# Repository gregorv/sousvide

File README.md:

# sousvide
An ATmega8 based Sous-Vide Temperature Controller

Sous-Vide is a cooking method for a very gentle preparation of meat and vegetables. The general idea is sealing the
food in a vacuum bed and then cooking it in a water bath with a maximum temperature of about 60°C to 70°C for an extended time.
Important cooking reactions (including sterilization) start at around 50°C, but unwanted processes (e.g. meat getting stringy)
increase above 70°C. Because of the lower temperatures the cooking time is elonged, but you get a very even and reproducible
result from the process.

## Overview
### Hardware
On the hardware side (schematics and layout KiCAD format) an ATmega8 regulates the temperature of the water bath with a TRIAC
controlled immersion heater. It is advised to use an acquarium water pump to better spread the heat in the bath. A DS18x2x type
Dallas 1Wire sensor is used for temperature monitoring. The UART can be used to communicate with a ESP8266 type WiFi module, but
is used in the prototype for serial communication and control.

### Firmware
A straight-forward, modularized fixed-point PID controller.

Uses the UART library from Peter Fleury, the 1wire library by Peter Dannegger and the libfixmath by Ben Brewer.

### PC Control Software
Qt5, QCustomPlot, nice.

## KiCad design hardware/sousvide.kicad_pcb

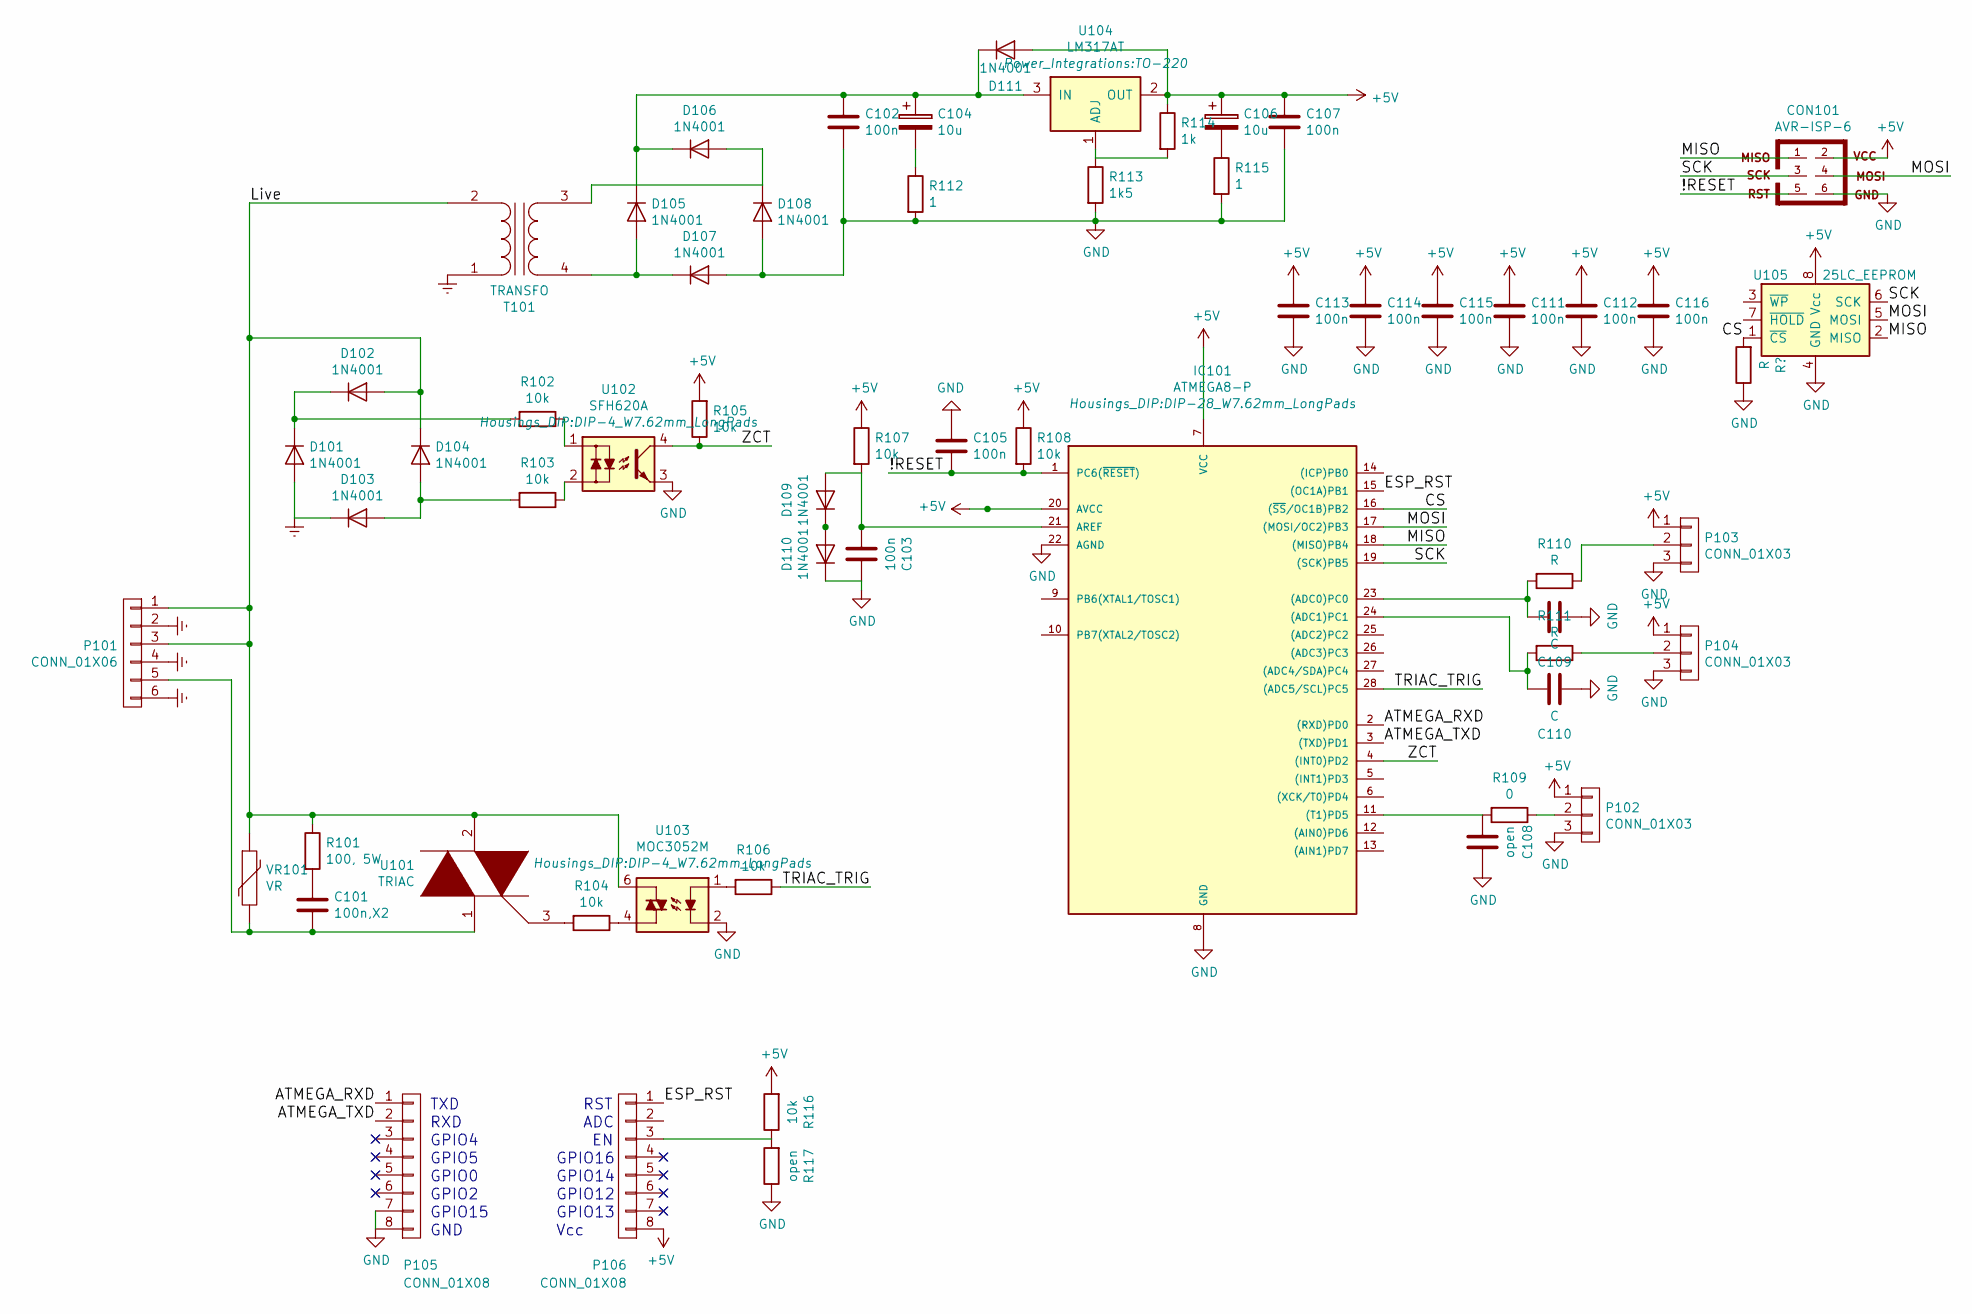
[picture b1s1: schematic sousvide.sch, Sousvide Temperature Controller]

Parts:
C101: 100n,X2; C_Rect_L18_W6_P15
C102, C103, C105, C107, C111, C112, C113, C114, C115, C116: 100n; C_0603_HandSoldering
C104, C106: 10u; TantalC_SizeB_EIA-3528_HandSoldering
C108: open; C_0603_HandSoldering
C109, C110: C; C_0603_HandSoldering
CON101: AVR-ISP-6; Pin_Header_Straight_2x03
D101, D102, D103, D104, D105, D106, D107, D108, D109, D110, D111: 1N4001; Diode_DO-41_SOD81_Horizontal_RM10
IC101: ATMEGA8-P; DIP-28_W7.62mm_LongPads
P101: CONN_01X06; TerminalBlock_Pheonix_MKDS1.5-6pol
P102, P103, P104: CONN_01X03; TerminalBlock_Pheonix_MKDS1.5-3pol
P105, P106: CONN_01X08; Connectors_JST_B8B-PH-K
R101: 100, 5W; Resistor_Horizontal_RM15mm
R102, R103, R104: 10k; Resistor_Horizontal_RM10mm
R105, R106, R107, R108, R116: 10k; R_0603_HandSoldering
R109: 0; R_0603_HandSoldering
R110, R111: R; R_0603_HandSoldering
R112, R115: 1; R_0603_HandSoldering
R113: 1k5; R_0603_HandSoldering
R114: 1k; R_0603_HandSoldering
R117: open; R_0603_HandSoldering
T101: TRANSFO; BLOCK_VB2,0_1_XX
U101: TRIAC; TO-220_Neutral123_Vertical_LargePads
U102: SFH620A; DIP-4_W7.62mm_LongPads
U103: MOC3052M; DIP-4_W7.62mm_LongPads
U104: LM317AT; TO-220
U105: 25LC_EEPROM; SOIC-8_3.9x4.9mm_Pitch1.27mm
VR101: VR; RV_Disc_D12_W4.2_P7.5

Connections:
+5V: C106.1, C107.1, C111.2, C112.2, C113.2, C114.2, C115.2, C116.2, CON101.2, D111.2 (A), IC101.7 (VCC), IC101.20 (AVCC), P102.1, P103.1, P104.1, P106.8, R105.2, R107.1, R108.1, R114.1, R116.2, U104.2 (OUT), U105.8 (Vcc)
/!RESET: C105.1, CON101.5, IC101.1 (PC6(~RESET~)), R108.2
/ATMEGA_RXD: IC101.2 ((RXD)PD0), P105.1
/ATMEGA_TXD: IC101.3 ((TXD)PD1), P105.2
/CS: IC101.16 ((~SS~/OC1B)PB2), U105.1 (~CS)
/ESP_RST: IC101.15 ((OC1A)PB1), P106.1
/Live: D102.2 (A), D104.1 (K), P101.1, P101.3, R101.1, T101.2 (AB), U101.2, U103.6, VR101.1
/MISO: CON101.1, IC101.18 ((MISO)PB4), U105.2 (MISO)
/MOSI: CON101.4, IC101.17 ((MOSI/OC2)PB3), U105.5 (MOSI)
/SCK: CON101.3, IC101.19 ((SCK)PB5), U105.6 (SCK)
/TRIAC_TRIG: IC101.28 ((ADC5/SCL)PC5), R106.1
/ZCT: IC101.4 ((INT0)PD2), R105.1, U102.4
Earth: D101.2 (A), D103.1 (K), P101.2, P101.4, P101.6, T101.1 (AA)
GND: C102.2, C103.1, C105.2, C107.2, C108.1, C109.2, C110.2, C111.1, C112.1, C113.1, C114.1, C115.1, C116.1, CON101.6, D107.2 (A), D108.2 (A), D110.1 (K), IC101.8 (GND), IC101.22 (AGND), P102.3, P103.3, P104.3, P105.7, P105.8, R112.2, R113.2, R115.2, R117.1, U102.3, U103.2, U105.4 (GND)
unnamed: C101.1, R101.2
unnamed: C101.2, P101.5, U101.1, VR101.2
unnamed: C102.1, C104.1, D105.1 (K), D106.1 (K), D111.1 (K), U104.3 (IN)
unnamed: C103.2, D109.2 (A), IC101.21 (AREF), R107.2
unnamed: C104.2, R112.1
unnamed: C106.2, R115.1
unnamed: C108.2, IC101.11 ((T1)PD5), R109.2
unnamed: C109.1, IC101.23 ((ADC0)PC0), R110.2
unnamed: C110.1, IC101.24 ((ADC1)PC1), R111.2
unnamed: D101.1 (K), D102.1 (K), R102.2
unnamed: D103.2 (A), D104.2 (A), R103.2
unnamed: D105.2 (A), D107.1 (K), T101.4 (SB)
unnamed: D106.2 (A), D108.1 (K), T101.3 (SA)
unnamed: D109.1 (K), D110.2 (A)
unnamed: P102.2, R109.1
unnamed: P103.2, R110.1
unnamed: P104.2, R111.1
unnamed: P106.3, R116.1, R117.2
unnamed: R102.1, U102.1
unnamed: R103.1, U102.2
unnamed: R104.1, U103.4
unnamed: R104.2, U101.3
unnamed: R106.2, U103.1
unnamed: R113.1, R114.2, U104.1 (ADJ)

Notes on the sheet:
RST
ADC
GPIO16
GPIO14
GPIO12
GPIO13
Vcc
TXD
RXD
GPIO4
GPIO5
GPIO0
GPIO2
GPIO15
GND

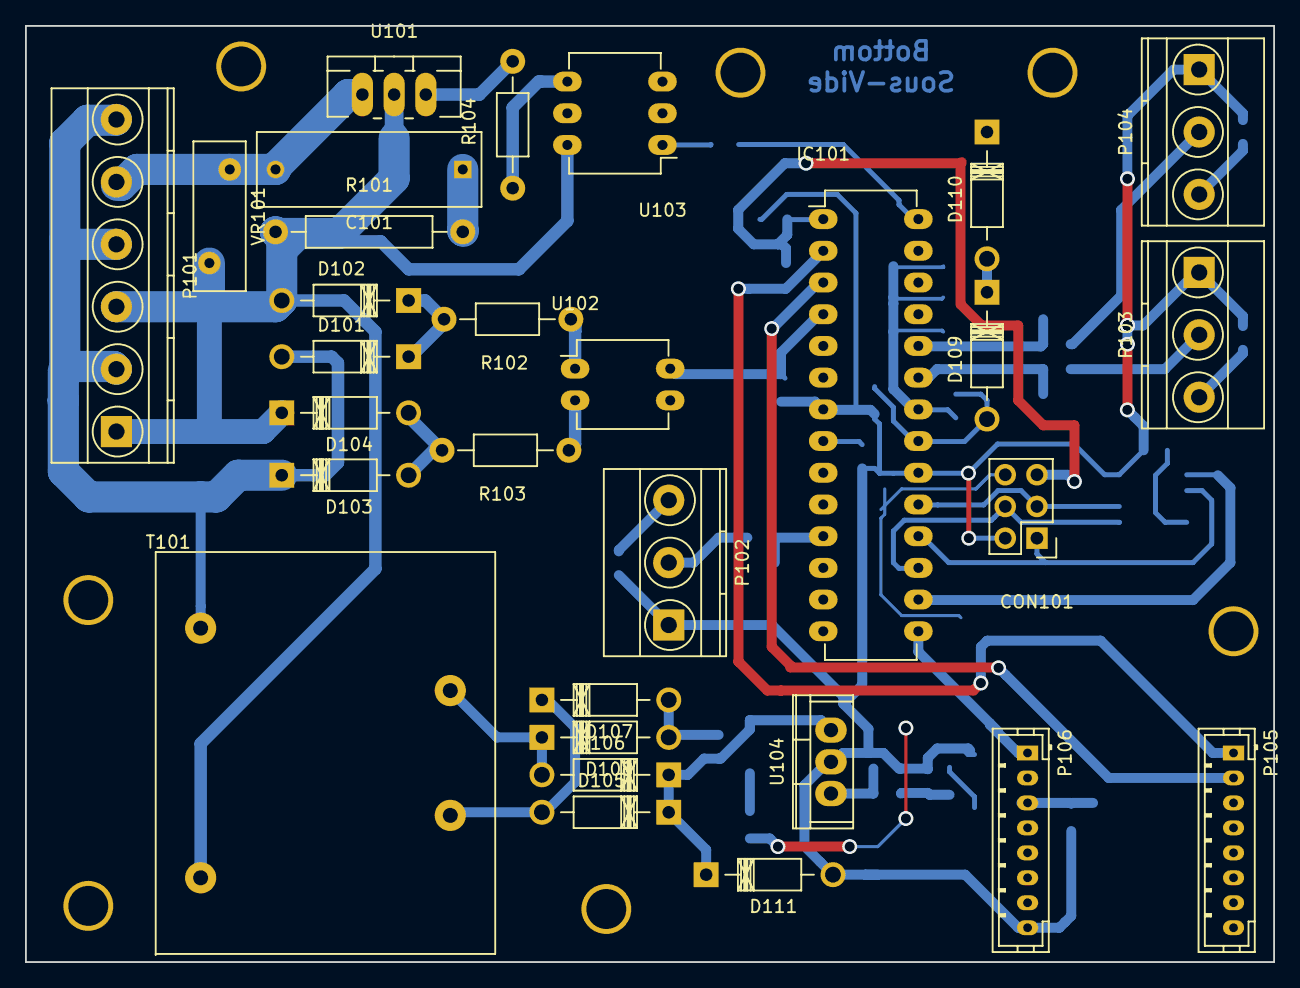
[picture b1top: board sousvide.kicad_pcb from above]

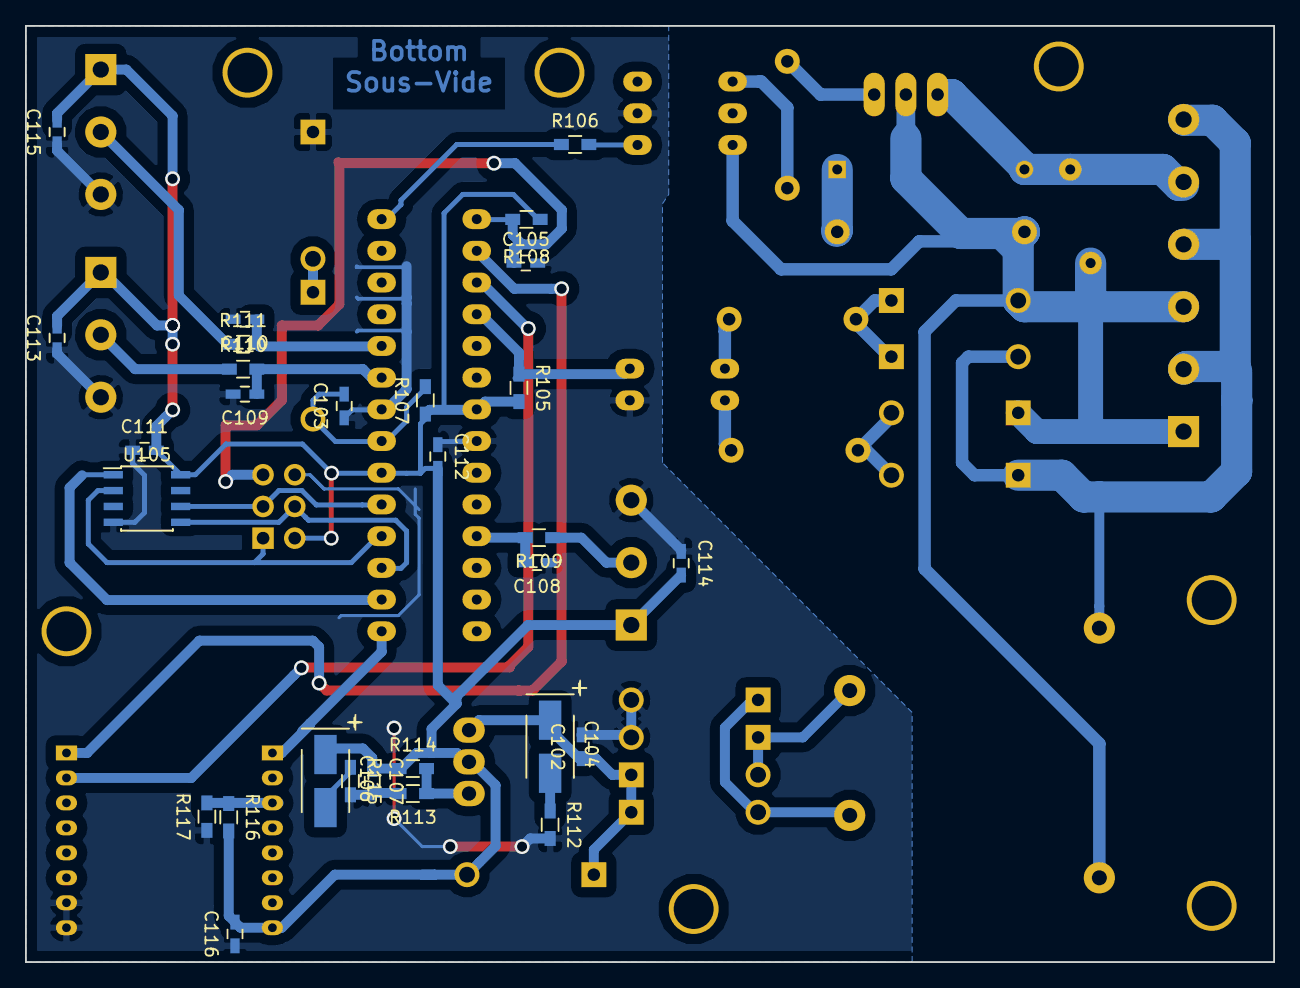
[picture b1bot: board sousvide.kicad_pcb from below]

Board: 2 copper layers, 100.0 x 75.0 mm, 66 parts (29 on the bottom side), 38 nets.

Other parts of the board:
DR?: drill_3-2
DR?#2, DR?#3, DR?#4, DR?#5, DR?#6, DR?#7: drill_3-2

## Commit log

2016-12-23 First revision of Sous-Vide firmware
2016-12-23 Moved firmware in subdirectory
2016-12-23 Added schematics, PCB layout and footprint library
2016-12-25 Removed old wifi code (for now?)
2016-12-25 Added libfixmath to project tree
2016-12-25 Started .gitignore
2016-12-25 Added onewire-library, updated main.c and Makefile
    onewire-library (1wire.(h,c), delay.(h,c) timebase.(h,c) by Peter
    Dannegger.
2016-12-25 Added Peter Fleurys UART library
2016-12-25 Removed binary libfixmath from repo and updated .gitignore
2016-12-28 Implemented PID controller
2016-12-28 libfixmath: Set some compiler #defines to remove unneccessary features
2016-12-28 Added serial communication module
    Handles and responds to commands over the UART interface.
2016-12-28 Main Program: Removed old code and included new modules
    Use control and com module and glue it together with onewire
    temperature readout.
2016-12-28 Removed linkage to vprintf
2016-12-28 Changed flash targets
    * Added target flash-fuses
    * Do not perform mandatory chip-erase, but make it configurable
    via the AVRDUDE_FLAGS variable
2016-12-28 Makefile: Moved all-target up, making it the default target
2016-12-28 Made makefile EEPROM image aware
2016-12-28 Various makefile-changes (lazy)
2016-12-28 Startet user application for controlling the souvide-device
    A small Qt5 based GUI application for setting and receiving the
    controller settings. An "extensive" visualisation (via QQustomPlot)
    is planned but not yet implemented.
2016-12-28 Fixed C warning messages
    Code (except for libfixmath) is now free of many optional GCC warnings.
    The flags pointer-sign and conversion are suppressed because they are
    problematic with Peter Danneggers 1wire code and libfixmath headers.
    The following warning flags are enabled:
    * -Wall
    * -Wpedantic
2016-12-28 Cleaned up main.h
    Removed unneccessary statements and old code. Documented weird definition
    block as required by 1wire library.
2016-12-28 Ignore EEPROM images
2016-12-28 Removed -Wno-pointer-sign flag from compilation
    Despite my previous commit message, code does not cause pointer-sign warnings.
2016-12-28 Switched on -Wconversion during compilation
2016-12-28 Fixed -Wconversion messages for libfixmath/fix16.h
2016-12-28 Fixed -Wconversion messages for com.c
    Requires a shit load of explicit casts...
2016-12-28 Added Licensing information and authors file
2016-12-29 Added support for a simple temperature plot
2016-12-31 Implemented temperature plot
2016-12-31 Changed thinOut time interval from 60ms to 60s :D
    Ooops
2017-01-01 Added version command and version number
    Can be used for scanning serial interfaces for a controller.
2017-01-01 Removed unused automaticly generated README
2017-01-01 Added FamFamFam's Silk Icon set
2017-01-01 Unused image file removed
2017-01-01 Added icon-resource to compilation
2017-01-01 Changed range to include negative D-constants for modification dialog
2017-01-01 ignore .bak* files from Qt Designer
2017-01-01 Improved control GUI
    * Reworked the overall style and organisation
    * Added icons
    * Automatic scanning for connected Sousvide-Devices
    * Added cooking timer
2017-01-01 Added very ugly annotated image from revision 1 of hardware prototype
    :)

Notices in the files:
hardware/sousvide.kicad_pcb:
(c) 2016 GPLv3
